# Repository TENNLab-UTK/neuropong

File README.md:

# Neuropong
This is the repo contains the NeuroPong project files. NeuroPong is an embedded, neuromorphic Atari (Pong) agent. It marries an event-based camera, TENNLab's Neuromorphic Starter Kit (https://arxiv.org/abs/2211.04526), and an Atari 2600 console. Spiking neural networks are trained on simulated events created from frames generated by the Arcade Learning Environment, and then, those spiking neural networks are put on hardware to examine how they perform in a live setting using real event camera inputs.

## Prerequisites
Repositories needed to run existing spiking neural network agents:

- TENNLab Open-Source Framework: https://github.com/TENNLab-UTK/framework-open
- Inivation `dv-processing` Library: https://gitlab.com/inivation/dv/dv-processing
- TENNLab Embedded Neuromorphic repository(*):
    - Needed to compile code for Neuromorphic Starter Kit's Raspberry Pi Picos

(*) You will need to get access to this repo from Jim Plank (jplank@utk.edu) until it is open-sourced.

You will also need Python and a shell of some kind (bash/zsh) on Linux or Mac. It is recommended to set up a python virtual environment (Python <= 3.9) for compatability with Inivation event camera library.

## Contents

- **/models**: STL models of 3D printed objects used in this project for the presented prototype

- **/kit-code**: Contains code used by `embedded-neuromorphic/` repo to compile kit code.

- **/pcb**: Repo containing KiCad files for the PCB that contains the Atari Translator circuit

- **/scripts**: Scripts used to assist with flashing Picos and compiling kit code. `calibration.py` and `event_server.py` are used on the Raspberry Pi (or whatever is communicating with the Neuromorphic Starter Kit)

- **/imgs**: Contains various diagrams and images detailing parts of the NeuroPong system

- **/networks**: Contains the networks generated for the Neuropong paper.  

## Table of Hardware Materials/Components

|    | Part              | Quantity | Cost |
|:--:| ----------------: | ------: | ----: |
|    | PCB Design        |  1   | $4.11 |
|    | AD5242           |   1   | $4.55 |
|    | ULN2008    |  1 (unused)   | $3.95 |
|    | Female pin strips |  2   | $26.00 |
|    | Raspberry Pi 4    |  1  | $75.00 |
|    | MicroSD Card    |  1   | $13.50 |
|    | Breakout Cable    |  1   | $20.00 |
|**Neuromorphic Starter Kit** |  |     |  |
|    | PCB Design |  1  | $10.65 |
|    | Raspberry Pi Pico | 3 | $15.00 |
|    | Power Supply | 1 | $7.69 |
| **Total** | | | $180.45 | 

* The Atari 2600 console and VideoOlympics cartridge together were ~$20.00.
* The DAVIS346 camera used for this project was purchased from [Inivation] (https://shop.inivation.com/).

## Running the Hardware Setup

1. Turn on monitor, put VideoOlympics cartridge in Atari 2600 console, and turn on the Atari console.
    - You should see the Pong game appear on the screen.
2. Plug NeuroPong controller into the back of one of the Atari controller ports.
    - *NOTE: you will need to make the NeuroPong cable. An detailed construction diagram can be found in the `/imgs` folder*
4. Power on the Raspberry Pi, and plug DAVIS346 camera into one of the USB ports on the Raspberry Pi.
5. Compile the network using `app_compile` from the `embedded_neuromorphic/` repo
    - Ex: `./bin/app_compile -j network_file -o kit-code/pico-pong_observations.c -a kit-code/pico-pong_actions[2,3].c -s`
6. Flash the three Raspberry Pi Picos on the kit with the appropriate encoder, decoder, and network. 
7. Power on the Neuromorphic Kit
8. On the Raspberry Pi, run `scripts/calibration.py` to assist with focusing the lens and cropping the camera's FOV to the screen.
    - The output produced by `scripts/calibration.py` is the command that is used to run `scripts/event_server.py`.
        - It figures out what the crop coordinates are and what the downsampling parameters need to be to match whatever the target downsampled resolution is. Target resolution is specified via global variables in the `scripts/calibration.py` program.
9. Run the command output by `scripts/calibration.py`
    - Ex: `python3 event_server.py --crop ...`
10. Wait 20-30 seconds for the system to initialize. If it's unreponsive, CTRL-C the event_server process and rerun it.
11. Begin the Atari game by toggling the ``Game Reset'' switch on the Atari system.
     
## Running the networks in the `framework-open` processor_tool

You may want to run the networks using `framework-open/bin/processor_tool` in order to view spike rasters for a network at each timestep during an episode of that network playing Pong in the Arcade Learning Environment. In `networks/processor_tool_commands` are the commands for the processor tool, for each of the 32 networks, for one 2000 frame Pong episode each. Each file in `networks/processor_tool_commands` contains the Apply_Spike (AS) commands that communicate the event simulated and downsampled representation of each frame as they're generated by the ALE online. To run, do the following:

            ```
            UNIX> pwd
            .../neuropong
            UNIX> ./framework-open/bin/processor_tool_risp < networks/processor_tool_commands/pong0.txt
            0   INPUT  :    // No inputs are provided to the network during the first frame or timestep, so the spike raster is empty
            1   INPUT  : 
            2   INPUT  : 
            3   INPUT  : 
            4   INPUT  : 
            5   INPUT  : 
            6   INPUT  : 
            7   INPUT  : 
            8   INPUT  : 
            9   INPUT  : 
            10  INPUT  : 
            11  INPUT  : 
            12  INPUT  : 
            13  INPUT  : 
            14  INPUT  : 
            15  INPUT  : 
            16  INPUT  : 
            17  INPUT  : 
            18  INPUT  : 
            19  INPUT  : 
            20  INPUT  : 
            21  INPUT  : 
            22  INPUT  : 
            23  INPUT  : 
            24  INPUT  : 
            25  INPUT  : 
            26  INPUT  : 
            27  INPUT  : 
            28  INPUT  : 
            29  INPUT  : 
            30  INPUT  : 
            31  INPUT  : 
            32  INPUT  : 
            33  INPUT  : 
            34  INPUT  : 
            35  INPUT  : 
            36  INPUT  : 
            37  INPUT  : 
            38  INPUT  : 
            39  INPUT  : 
            40  INPUT  : 
            41  INPUT  : 
            42  INPUT  : 
            43  INPUT  : 
            44  INPUT  : 
            45  INPUT  : 
            46  INPUT  : 
            47  INPUT  : 
            48  INPUT  : 
            49  INPUT  : 
            50  INPUT  : 
            51  INPUT  : 
            52  INPUT  : 
            53  INPUT  : 
            54  INPUT  : 
            55  INPUT  : 
            56  INPUT  : 
            57  INPUT  : 
            58  INPUT  : 
            59  INPUT  : 
            60  INPUT  : 
            61  INPUT  : 
            62  INPUT  : 
            63  INPUT  : 
            64  INPUT  : 
            65  INPUT  : 
            66  INPUT  : 
            67  INPUT  : 
            68  INPUT  : 
            69  INPUT  : 
            70  INPUT  : 
            71  INPUT  : 
            72  INPUT  : 
            73  INPUT  : 
            74  INPUT  : 
            75  INPUT  : 
            76  INPUT  : 
            77  INPUT  : 
            78  INPUT  : 
            79  INPUT  : 
            80  INPUT  : 
            81  INPUT  : 
            82  INPUT  : 
            83  INPUT  : 
            84  INPUT  : 
            85  INPUT  : 
            86  INPUT  : 
            87  INPUT  : 
            88  INPUT  : 
            89  INPUT  : 
            90  INPUT  : 
            91  INPUT  : 
            92  INPUT  : 
            93  INPUT  : 
            94  INPUT  : 
            95  INPUT  : 
            96  INPUT  : 
            97  INPUT  : 
            98  INPUT  : 
            99  INPUT  : 
            100 INPUT  : 
            101 INPUT  : 
            102 INPUT  : 
            103 INPUT  : 
            104 INPUT  : 
            105 INPUT  : 
            106 INPUT  : 
            107 INPUT  : 
            108 INPUT  : 
            109 INPUT  : 
            110 INPUT  : 
            111 INPUT  : 
            112 INPUT  : 
            113 INPUT  : 
            114 INPUT  : 
            115 INPUT  : 
            116 INPUT  : 
            117 INPUT  : 
            118 INPUT  : 
            119 INPUT  : 
            120 INPUT  : 
            121 INPUT  : 
            122 INPUT  : 
            123 INPUT  : 
            124 INPUT  : 
            125 INPUT  : 
            126 INPUT  : 
            127 INPUT  : 
            128 INPUT  : 
            129 INPUT  : 
            130 INPUT  : 
            131 INPUT  : 
            132 INPUT  : 
            133 INPUT  : 
            134 INPUT  : 
            135 INPUT  : 
            136 INPUT  : 
            137 INPUT  : 
            138 INPUT  : 
            139 INPUT  : 
            140 INPUT  : 
            141 INPUT  : 
            142 INPUT  : 
            143 INPUT  : 
            144 INPUT  : 
            145 INPUT  : 
            146 INPUT  : 
            147 INPUT  : 
            148 INPUT  : 
            149 INPUT  : 
            150 INPUT  : 
            151 INPUT  : 
            152 INPUT  : 
            153 INPUT  : 
            154 INPUT  : 
            155 INPUT  : 
            156 INPUT  : 
            157 INPUT  : 
            158 INPUT  : 
            159 INPUT  : 
            160 OUTPUT : 
            161 OUTPUT : 
            162 OUTPUT : 
            0   INPUT  : 1000000000100100100000000000000000000000000000000 // Now, during the second frame/timestep, we apply a spike to  
            1   INPUT  : 1000000000000000000000000000000000000000000000000 // the appropriate input neurons and run the network for 50 cycles. 
            2   INPUT  : 1010000001000000010011000000000010000000000000000 // The columns represent the network timestep 
            3   INPUT  : 1000000000000000000000000000000000000000000000000 // and a "1" represents a neuronal fire.
            4   INPUT  : 1000000000000111100100100000001000100000000001000
            5   INPUT  : 1000000000000000000000000000000000000000000000000
            6   INPUT  : 1000000000000000000000000000000000000000000000000
            7   INPUT  : 1000000000000000000000000000000000000000000000000
            8   INPUT  : 1000000000000000000000000000000000000000000000000
            9   INPUT  : 1000000000000000000000000000000000000000000000000
            10  INPUT  : 1000000000000000000000000000000000000000000000000
            11  INPUT  : 1000000000000000000000000000000000000000000000000
            12  INPUT  : 1000000000000000000000000000000000000000000000000
            13  INPUT  : 1000000000000000000000000000000000000000000000000
            14  INPUT  : 1000000000000000000000000000000000000000000000000
            15  INPUT  : 1000000000000000000000000000000000000000000000000
            16  INPUT  : 1000000000100000000000000000000000000000000000000
            17  INPUT  : 1000000000000000000000000000000000000000000000000
            18  INPUT  : 1000000000000000000000000000000000000000000000000
            19  INPUT  : 1000000000000000000000000000000000000000000000000
            20  INPUT  : 1000000000000010000000000000000000000000000000000
            21  INPUT  : 1000000000000000000000000000000000000000000000000
            22  INPUT  : 1000000001000000000000000000000000000000000000000
            23  INPUT  : 1001000000000000000000000000000000000000000000000
            24  INPUT  : 1000000000000000000000000000000000000000000000000
            25  INPUT  : 1000000000000000000000000000000000000000000000000
            26  INPUT  : 1000000000000000000000000000000000000000000000000
            27  INPUT  : 1000010000000000000000000000000000000000000000000
            28  INPUT  : 1000000000000000000000000000000000000000000000000
            29  INPUT  : 1000000001010000000000000000000000000000000000000
            30  INPUT  : 1000000000000000000000000000000000000000000000000
            31  INPUT  : 1000000000000000000000000000000000000000000000000
            32  INPUT  : 1000000000000000000000000000000000000000000000000
            33  INPUT  : 1000000000000000000000000000000000000000000000000
            34  INPUT  : 1000000000000000000000000000000000000000000000000
            35  INPUT  : 1000000000000000000000000000000000000000000000000
            36  INPUT  : 1000000000000000000000000000000000000000000000000
            37  INPUT  : 1000000000000000000000000000000000000000000000000
            38  INPUT  : 1000000010000000000000000000000000000000000000000
            39  INPUT  : 1000000000000000000000000000000000000000000000000
            40  INPUT  : 1000000000010000000000000000000000000000000000000
            41  INPUT  : 1000000000000000000000000000000000000000000000000
            42  INPUT  : 1000000000000000000000000000000000000000000000000
            43  INPUT  : 1000000000000000000000000000000000000000000000000
            44  INPUT  : 1000000000000000000000000000000000000000000000000
            45  INPUT  : 1000000000000000000000000000000000000000000000000
            46  INPUT  : 1000000000000000000000000000000000000000000000000
            47  INPUT  : 1000000000000000000000000000000000000000000000000
            48  INPUT  : 1000000000010000000000000000000000000000000000000
            49  INPUT  : 1000000000000000000000000000000000000000000000000
            50  INPUT  : 1000000000010000000000000000000000000000000000000
            51  INPUT  : 1000000100000000000000000000000000000000000000000
            52  INPUT  : 1000000000000000000000000000000000000000000000000
            53  INPUT  : 1000000000000000000000000000000000000000000000000
            54  INPUT  : 1000000000000000000000000000000000000000000000000
            55  INPUT  : 1000000000000000000000000000000000000000000000000
            56  INPUT  : 1000000000000000000000000000000000000000000000000
            57  INPUT  : 1000000000000000000000000000000000000000000000000
            58  INPUT  : 1001010000000110000000000001111001001000000010001
            59  INPUT  : 1000100000000001000000000000000000000000000000000
            60  INPUT  : 1000000000000000000000000000000000000000000000000
            61  INPUT  : 1000000000010000000000000000000000000000000000000
            62  INPUT  : 1000000000000000000000000000000000000000000000000
            63  INPUT  : 1000000000000000000000000000000000000000000000000
            64  INPUT  : 1100010100100100000000000000000000000000000000000
            65  INPUT  : 1000000000000000000000000000000000000000000000000
            66  INPUT  : 1010010010000000000000000000000000000000000000000
            67  INPUT  : 1000000000010000000000000000000000000000000000000
            68  INPUT  : 1000000000000000000000000000000000000000000000000
            69  INPUT  : 1001000000000000000000000000000000000000000000000
            70  INPUT  : 1000010000000000000000000000000000000000000000000
            71  INPUT  : 1000000000000000000000000000000000000000000000000
            72  INPUT  : 1000000000000000000000000000000000000000000000000
            73  INPUT  : 1000000000000000000000000000000000000000000000000
            74  INPUT  : 1000000000000000000000000000000000000000000000000
            75  INPUT  : 1000000000000001000000000000000000000000000000000
            76  INPUT  : 1000000000000000000000000000000000000000000000000
            77  INPUT  : 1000000000000000000000000000000000000000000000000
            78  INPUT  : 1001011000100000000000000100000000000000000000000
            79  INPUT  : 1000000000000000000000000000000000000000000000000
            80  INPUT  : 1000000000000000000000000000000000000000000000000
            81  INPUT  : 1000000000000000000000000000000000000000000000000
            82  INPUT  : 1000000000000000000000000000000000000000000000000
            83  INPUT  : 1000000000000000000000000000000000000000000000000
            84  INPUT  : 1000000000000000000000000000000000000000000000000
            85  INPUT  : 1000000000000000000000000000000000000000000000000
            86  INPUT  : 1000000000000000000000000000000000000000000000000
            87  INPUT  : 1000000000000000000000000000000000000000000000000
            88  INPUT  : 1000000000000000000000000000000000000000000000000
            89  INPUT  : 1000000000000000000000000000000000000000000000000
            90  INPUT  : 1000000000000000000000000000000000000000000000000
            91  INPUT  : 1000000000000000000000000000000000000000000000000
            92  INPUT  : 1000000000000000000000000000000000000000000000000
            93  INPUT  : 1000000000000000000000000000000000000000000000000
            94  INPUT  : 1000000000000000000000000000000000000000000000000
            95  INPUT  : 1000000000000000000000000000000000000000000000000
            96  INPUT  : 1000000000100001000000000010000000000000000000000
            97  INPUT  : 1000000000000000000000000000000000000000000000000
            98  INPUT  : 1010000000000000000000000000000000000000000000000
            99  INPUT  : 1000000000000000000000000000000000000000000000000
            100 INPUT  : 1000000000000000000000000000000000000000000000000
            101 INPUT  : 1000000100000000000000000000000000000000000000000
            102 INPUT  : 1000000000000000000000000000000000000000000000000
            103 INPUT  : 1000000000000000000000000000000000000000000000000
            104 INPUT  : 1000000000000000000000000000000000000000000000000
            105 INPUT  : 1000000000000000000000000000000000000000000000000
            106 INPUT  : 1000000000000000000000000000000000000000000000000
            107 INPUT  : 1000000000000000000000000000000000000000000000000
            108 INPUT  : 1000000000000000000000000000000000000000000000000
            109 INPUT  : 1000000000000000000000000000000000000000000000000
            110 INPUT  : 1000000000000000000000000000000000000000000000000
            111 INPUT  : 1000000000000000000000000000000000000000000000000
            112 INPUT  : 1000000000000000000000000000000000000000000000000
            113 INPUT  : 1001001000000000000000000000000000000000000000000
            114 INPUT  : 1000000000000000000000000000000000000000000000000
            115 INPUT  : 1000000000000000000000000000000000000000000000000
            116 INPUT  : 1000000000000000000000000000000000000000000000000
            117 INPUT  : 1000000000000000000000000000000000000000000000000
            118 INPUT  : 1000000000100000000000010000000000100000000000000
            119 INPUT  : 1000000000000000000000000000000000000000000000000
            120 INPUT  : 1000000000000100000000001000000000000000000000000
            121 INPUT  : 1000000000000000000000000000000000000000000000000
            122 INPUT  : 1010000000000000010000000000000000000000000000000
            123 INPUT  : 1000000000000000000000000000000000000000000000000
            124 INPUT  : 1000000000000000000000000000000000000000000000000
            125 INPUT  : 1000000000000000000000000000000000000000000000000
            126 INPUT  : 1000000000000000000000000000000000000000000000000
            127 INPUT  : 1000000000000000000000000000000000000000000000000
            128 INPUT  : 1000000000000000000000000000000000000000000000000
            129 INPUT  : 1011000100000000000000100000000000000000000000000
            130 INPUT  : 1000000000000000000000000000000000000000000000000
            131 INPUT  : 1000000000000000000000000000000000000000000000000
            132 INPUT  : 1000000000000000000000000000000000000000000000000
            133 INPUT  : 1000000000000001000000000000000000000000000000000
            134 INPUT  : 1000000000000000000000000000000000000000000000000
            135 INPUT  : 1010000000000000000000000000000000000000000000000
            136 INPUT  : 1000000000000000000000000000000000000000000000000
            137 INPUT  : 1000000000000000000000000000000000000000000000000
            138 INPUT  : 1000000000000000000000000000000000000000000000000
            139 INPUT  : 1000000000000000000000000000000000000000000000000
            140 INPUT  : 1000000000000000000000000000000000000000000000000
            141 INPUT  : 1000000000000000000000000000000000000000000000000
            142 INPUT  : 1000000010000000000000000000000000000000000000000
            143 INPUT  : 1000000000000000000000000000000000000000000000000
            144 INPUT  : 1000000100000001000100000000001000000000000000000
            145 INPUT  : 1000000000000000000000000000000000000000000000000
            146 INPUT  : 1000000000000000000000000000000000000000000000000
            147 INPUT  : 1000000000000000000000000000000000000000000000000
            148 INPUT  : 1000100000000000000000000000000000000000000000000
            149 INPUT  : 1000000000000000000000000000000000000000000000000
            150 INPUT  : 1100010000000000000010000000000000000000000000000
            151 INPUT  : 1000000000000000000000000000000000000000000000000
            152 INPUT  : 1000000000000000000000000000000000000000000000000
            153 INPUT  : 1000000000000000000000000000000000000000000000000
            154 INPUT  : 1010000000000000000000000000000000000000000000000
            155 INPUT  : 1000000000000000000000000000000000000000000000000
            156 INPUT  : 1000000000000000000000000000000000000000000000000
            157 INPUT  : 1000000000000000000000000000000000000000000000000
            158 INPUT  : 1000000100000010000000000000000000000000000000000
            159 INPUT  : 1000000000000000000000000000000000000000000000000
            160 OUTPUT : 0000100101000000011000000000000111100100100000001 // At the end of our 50 timesteps, we count the output fires on the
            161 OUTPUT : 0000000010000000000000000000000000000000000000000 // three output neurons. Whoever fired the most "wins", and its
            162 OUTPUT : 0000000001000100000000000000000000000000000000000 // action is the action performed by the network for that frame
            ...                                                            // from the ALE.
            ...
            ```

More information about `processor_tool_risp` can be found in the `framework-open/markdown/` directory. This is provided as a method for you to see how the network acts when provided event-simulated and downsampled ALE frames.

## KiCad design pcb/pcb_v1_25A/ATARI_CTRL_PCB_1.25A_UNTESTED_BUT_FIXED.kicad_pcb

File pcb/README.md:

# Atari CTRL PCB
This folder contains the KiCad source files along with some renders of what the PCB looks like

# Components
1. Digital Potentiometer - AD5242
    - Function: Emulate paddle controller analogue signal
    - https://www.digikey.com/en/products/detail/analog-devices-inc/AD5242BRUZ1M/997427?s=N4IgTCBcDaIKwAY4FoCCAROYAsYBCASgKoBaAjALLIBy6IAugL5A
2. Darlington Transistor Pair - ULN2003A
    - Function: Emulate button presses from joystick controller (negative logic)
    - Note: When button is pressed, the input pin (UP/DOWN/LEFT/RIGHT/FIRE) is shorted from floating voltage to ground (0 V)
    - https://www.digikey.com/en/products/detail/texas-instruments/ULN2003ADR/277011

## Case Incompatability Disclosure 
**NOTE**: The PCB Case Lid is only compatible with 1.25A version of the case. This is due to the connector size changes from 2.00mm connector (v1.27) to a 2.54mm connector (1.37A). 

## Pinout Disclosure
**NOTE**: The PCB design does not utilize the 5V rail from the Atari to avoid voltage mismatches on the digital potentiometer output.

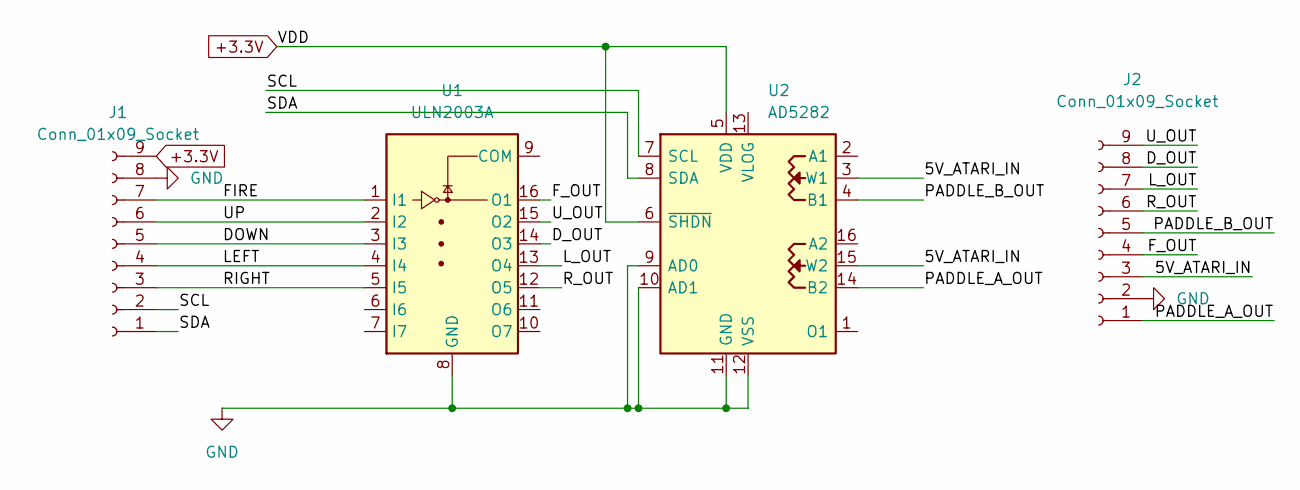
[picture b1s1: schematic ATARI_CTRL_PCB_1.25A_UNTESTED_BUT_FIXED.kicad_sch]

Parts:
J1, J2: Conn_01x09_Socket; PinSocket_1x09_P2.00mm_Vertical
U1: ULN2003A; SOIC-16_3.9x9.9mm_P1.27mm
U2: AD5282; TSSOP-16_4.4x5mm_P0.65mm

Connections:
+3.3V: J1.9, U2.5 (VDD), U2.6 (~SHDN)
/5V_ATARI_IN: J2.3, U2.3 (W1), U2.15 (W2)
/DOWN: J1.5, U1.3 (I3)
/D_OUT: J2.8, U1.14 (O3)
/FIRE: J1.7, U1.1 (I1)
/F_OUT: J2.4, U1.16 (O1)
/LEFT: J1.4, U1.4 (I4)
/L_OUT: J2.7, U1.13 (O4)
/PADDLE_A_OUT: J2.1, U2.14 (B2)
/PADDLE_B_OUT: J2.5, U2.4 (B1)
/RIGHT: J1.3, U1.5 (I5)
/R_OUT: J2.6, U1.12 (O5)
/SCL: J1.2, U2.7 (SCL)
/SDA: J1.1, U2.8 (SDA)
/UP: J1.6, U1.2 (I2)
/U_OUT: J2.9, U1.15 (O2)
GND: J1.8, J2.2, U1.8 (GND), U2.9 (AD0), U2.10 (AD1), U2.11 (GND), U2.12 (VSS)

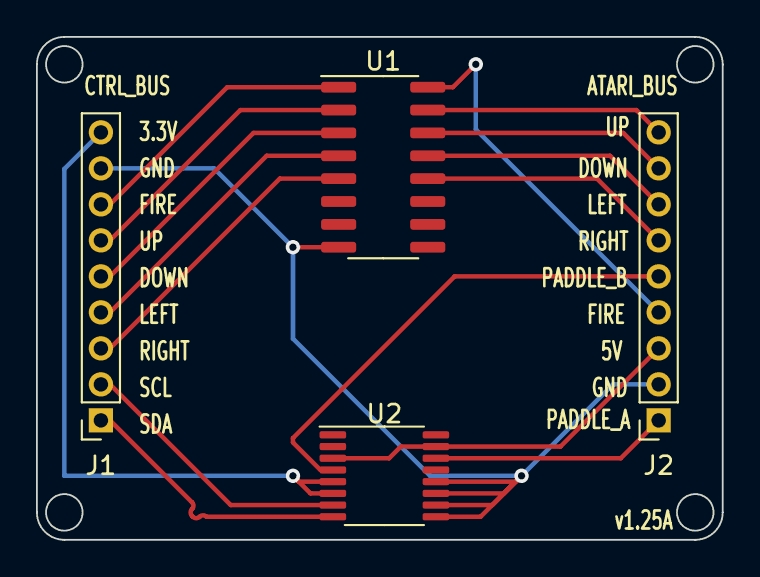
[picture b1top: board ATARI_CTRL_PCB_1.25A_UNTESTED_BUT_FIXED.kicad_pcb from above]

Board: 2 copper layers, 38.1 x 27.9 mm, 4 parts (0 on the bottom side), 17 nets.

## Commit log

2025-02-26 Initial repo push
2025-02-27 Adding link to Neuromorphic Starter Kit arxiv paper
2025-03-01 NeuroPong cable - Update README.md
2025-03-01 neuropong cable diagram for readme
2025-03-03 Create LICENSE
2025-03-05 Adding networks and processor_tool commands to run the networks in software
2025-03-05 Getting rid of .so file
